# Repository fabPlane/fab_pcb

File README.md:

Images referenced from the description of fabPlane/fab_pcb PR #34 (kept off main).

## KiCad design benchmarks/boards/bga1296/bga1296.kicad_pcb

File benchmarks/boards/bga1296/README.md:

# Eight-layer 1,296-net BGA keepout candidate

Original MIT fixture, seed 6596. A 36 × 36 BGA at 0.5 mm pitch drives
1,296 shuffled two-terminal nets to four destination banks (2,592 pads total).
The 90 × 90 mm board has eight signal copper layers, 0.10/0.10 mm track/clearance
and 0.30/0.10 mm through vias. Two 3 × 28 mm routing keepouts at x=29–32 and
x=58–61, y=31–59 forbid tracks and vias on every copper layer. Routes can pass
around their ends. This increases input size and adds constraints relative to
the earlier 1,024-net candidate; relative routing difficulty is not established.

The companion project is required. No planes, differential pairs, matched
lengths, footprint libraries or external board sources are used. The generator
loads the board, checks net ownership, stack, effective rules, rule-area masks,
and native connectivity, then runs a fresh native DRC. It also requires all 16
keepout polygons in the exported DSN, with exact micrometre coordinates,
layer multiplicity, zero aperture, and closed rectangular vertex sequences.
This fixture-specific check intentionally rejects alternate export grammars. Board, project and DSN are deterministic
across output directories.

KiCad 10.0.6 reports 1,296 native connectivity opens but caps the DRC JSON at
499 unconnected findings. The zero geometry errors and warnings admit the input;
the capped report does not establish exact routed opens or native completion.
There is no best-known complete, DRC-clean routing yet. Keep this board outside
the frozen suite and do not promote it to a feasible scored tier.

## Generate and verify

Requires `/usr/bin/python3` with `pcbnew`, and `kicad-cli` 10.0.6. Use a fresh output
directory. No network access is needed.

```sh
nice -n 10 taskset -c 0-5 timeout 150 /usr/bin/python3 -O benchmarks/boards/bga1296/generate.py /tmp/bga1296-new --seed 6596
nice -n 10 taskset -c 0-5 timeout 180 /usr/bin/python3 -O -m unittest discover -s benchmarks/boards/bga1296 -p 'test_*.py'
```

The measurement compares the same placement, nets, seed and rules with and
without the two keepouts, three fresh runs per router and variant. Full-corpus
measurements preserve the existing five bundled suites. See the PR assets for
exact source pins, results and limitations. Native baseline denominator adoption
remains pending; this fixture does not change scoring or ranking.

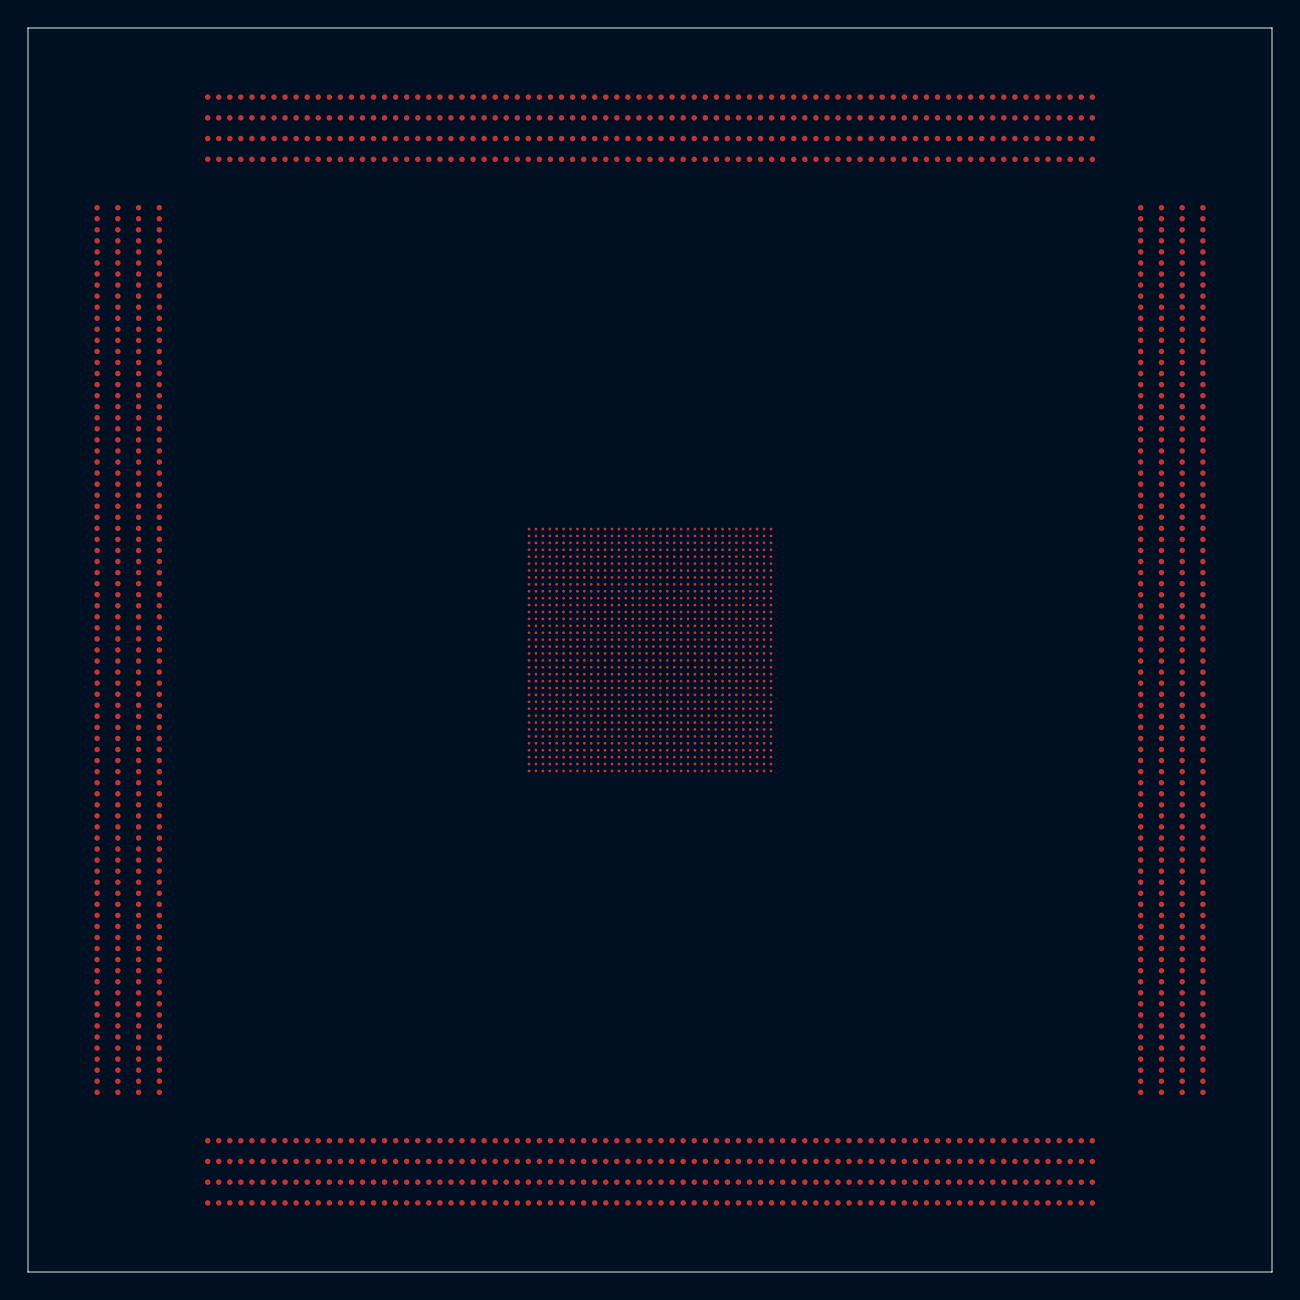
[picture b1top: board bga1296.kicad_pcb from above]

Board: 8 copper layers, 90.0 x 90.0 mm, 1297 parts (0 on the bottom side), 1296 nets, no tracks yet.

Parts:
J1, J2, J3, J4, J5, J6, J7, J8, J9, J10, J11, J12, J13, J14, J15, J16, J17, J18, J19, J20, J21, J22, J23, J24, J25, J26, J27, J28, J29, J30, J31, J32, J33, J34, J35, J36, J37, J38, J39, J40, J41, J42, J43, J44, J45, J46, J47, J48, J49, J50, J51, J52, J53, J54, J55, J56, J57, J58, J59, J60, J61, J62, J63, J64, J65, J66, J67, J68, J69, J70, J71, J72, J73, J74, J75, J76, J77, J78, J79, J80, J81, J82, J83, J84, J85, J86, J87, J88, J89, J90, J91, J92, J93, J94, J95, J96, J97, J98, J99, J100, J101, J102, J103, J104, J105, J106, J107, J108, J109, J110, J111, J112, J113, J114, J115, J116, J117, J118, J119, J120, J121, J122, J123, J124, J125, J126, J127, J128, J129, J130, J131, J132, J133, J134, J135, J136, J137, J138, J139, J140, J141, J142, J143, J144, J145, J146, J147, J148, J149, J150, J151, J152, J153, J154, J155, J156, J157, J158, J159, J160, J161, J162, J163, J164, J165, J166, J167, J168, J169, J170, J171, J172, J173, J174, J175, J176, J177, J178, J179, J180, J181, J182, J183, J184, J185, J186, J187, J188, J189, J190, J191, J192, J193, J194, J195, J196, J197, J198, J199, J200, J201, J202, J203, J204, J205, J206, J207, J208, J209, J210, J211, J212, J213, J214, J215, J216, J217, J218, J219, J220, J221, J222, J223, J224, J225, J226, J227, J228, J229, J230, J231, J232, J233, J234, J235, J236, J237, J238, J239, J240, J241, J242, J243, J244, J245, J246, J247, J248, J249, J250, J251, J252, J253, J254, J255, J256, J257, J258, J259, J260, J261, J262, J263, J264, J265, J266, J267, J268, J269, J270, J271, J272, J273, J274, J275, J276, J277, J278, J279, J280, J281, J282, J283, J284, J285, J286, J287, J288, J289, J290, J291, J292, J293, J294, J295, J296, J297, J298, J299, J300, J301, J302, J303, J304, J305, J306, J307, J308, J309, J310, J311, J312, J313, J314, J315, J316, J317, J318, J319, J320, J321, J322, J323, J324, J325, J326, J327, J328, J329, J330, J331, J332, J333, J334, J335, J336, J337, J338, J339, J340, J341, J342, J343, J344, J345, J346, J347, J348, J349, J350, J351, J352, J353, J354, J355, J356, J357, J358, J359, J360, J361, J362, J363, J364, J365, J366, J367, J368, J369, J370, J371, J372, J373, J374, J375, J376, J377, J378, J379, J380, J381, J382, J383, J384, J385, J386, J387, J388, J389, J390, J391, J392, J393, J394, J395, J396, J397, J398, J399, J400, J401, J402, J403, J404, J405, J406, J407, J408, J409, J410, J411, J412, J413, J414, J415, J416, J417, J418, J419, J420, J421, J422, J423, J424, J425, J426, J427, J428, J429, J430, J431, J432, J433, J434, J435, J436, J437, J438, J439, J440, J441, J442, J443, J444, J445, J446, J447, J448, J449, J450, J451, J452, J453, J454, J455, J456, J457, J458, J459, J460, J461, J462, J463, J464, J465, J466, J467, J468, J469, J470, J471, J472, J473, J474, J475, J476, J477, J478, J479, J480, J481, J482, J483, J484, J485, J486, J487, J488, J489, J490, J491, J492, J493, J494, J495, J496, J497, J498, J499, J500, J501, J502, J503, J504, J505, J506, J507, J508, J509, J510, J511, J512, J513, J514, J515, J516, J517, J518, J519, J520, J521, J522, J523, J524, J525, J526, J527, J528, J529, J530, J531, J532, J533, J534, J535, J536, J537, J538, J539, J540, J541, J542, J543, J544, J545, J546, J547, J548, J549, J550, J551, J552, J553, J554, J555, J556, J557, J558, J559, J560, J561, J562, J563, J564, J565, J566, J567, J568, J569, J570, J571, J572, J573, J574, J575, J576, J577, J578, J579, J580, J581, J582, J583, J584, J585, J586, J587, J588, J589, J590, J591, J592, J593, J594, J595, J596, J597, J598, J599, J600, J601, J602, J603, J604, J605, J606, J607, J608, J609, J610, J611, J612, J613, J614, J615, J616, J617, J618, J619, J620, J621, J622, J623, J624, J625, J626, J627, J628, J629, J630, J631, J632, J633, J634, J635, J636, J637, J638, J639, J640, J641, J642, J643, J644, J645, J646, J647, J648, J649, J650, J651, J652, J653, J654, J655, J656, J657, J658, J659, J660, J661, J662, J663, J664, J665, J666, J667, J668, J669, J670, J671, J672, J673, J674, J675, J676, J677, J678, J679, J680, J681, J682, J683, J684, J685, J686, J687, J688, J689, J690, J691, J692, J693, J694, J695, J696, J697, J698, J699, J700, J701, J702, J703, J704, J705, J706, J707, J708, J709, J710, J711, J712, J713, J714, J715, J716, J717, J718, J719, J720, J721, J722, J723, J724, J725, J726, J727, J728, J729, J730, J731, J732, J733, J734, J735, J736, J737, J738, J739, J740, J741, J742, J743, J744, J745, J746, J747, J748, J749, J750, J751, J752, J753, J754, J755, J756, J757, J758, J759, J760, J761, J762, J763, J764, J765, J766, J767, J768, J769, J770, J771, J772, J773, J774, J775, J776, J777, J778, J779, J780, J781, J782, J783, J784, J785, J786, J787, J788, J789, J790, J791, J792, J793, J794, J795, J796, J797, J798, J799, J800, J801, J802, J803, J804, J805, J806, J807, J808, J809, J810, J811, J812, J813, J814, J815, J816, J817, J818, J819, J820, J821, J822, J823, J824, J825, J826, J827, J828, J829, J830, J831, J832, J833, J834, J835, J836, J837, J838, J839, J840, J841, J842, J843, J844, J845, J846, J847, J848, J849, J850, J851, J852, J853, J854, J855, J856, J857, J858, J859, J860, J861, J862, J863, J864, J865, J866, J867, J868, J869, J870, J871, J872, J873, J874, J875, J876, J877, J878, J879, J880, J881, J882, J883, J884, J885, J886, J887, J888, J889, J890, J891, J892, J893, J894, J895, J896, J897, J898, J899, J900, J901, J902, J903, J904, J905, J906, J907, J908, J909, J910, J911, J912, J913, J914, J915, J916, J917, J918, J919, J920, J921, J922, J923, J924, J925, J926, J927, J928, J929, J930, J931, J932, J933, J934, J935, J936, J937, J938, J939, J940, J941, J942, J943, J944, J945, J946, J947, J948, J949, J950, J951, J952, J953, J954, J955, J956, J957, J958, J959, J960, J961, J962, J963, J964, J965, J966, J967, J968, J969, J970, J971, J972, J973, J974, J975, J976, J977, J978, J979, J980, J981, J982, J983, J984, J985, J986, J987, J988, J989, J990, J991, J992, J993, J994, J995, J996, J997, J998, J999, J1000, J1001, J1002, J1003, J1004, J1005, J1006, J1007, J1008, J1009, J1010, J1011, J1012, J1013, J1014, J1015, J1016, J1017, J1018, J1019, J1020, J1021, J1022, J1023, J1024, J1025, J1026, J1027, J1028, J1029, J1030, J1031, J1032, J1033, J1034, J1035, J1036, J1037, J1038, J1039, J1040, J1041, J1042, J1043, J1044, J1045, J1046, J1047, J1048, J1049, J1050, J1051, J1052, J1053, J1054, J1055, J1056, J1057, J1058, J1059, J1060, J1061, J1062, J1063, J1064, J1065, J1066, J1067, J1068, J1069, J1070, J1071, J1072, J1073, J1074, J1075, J1076, J1077, J1078, J1079, J1080, J1081, J1082, J1083, J1084, J1085, J1086, J1087, J1088, J1089, J1090, J1091, J1092, J1093, J1094, J1095, J1096, J1097, J1098, J1099, J1100, J1101, J1102, J1103, J1104, J1105, J1106, J1107, J1108, J1109, J1110, J1111, J1112, J1113, J1114, J1115, J1116, J1117, J1118, J1119, J1120, J1121, J1122, J1123, J1124, J1125, J1126, J1127, J1128, J1129, J1130, J1131, J1132, J1133, J1134, J1135, J1136, J1137, J1138, J1139, J1140, J1141, J1142, J1143, J1144, J1145, J1146, J1147, J1148, J1149, J1150, J1151, J1152, J1153, J1154, J1155, J1156, J1157, J1158, J1159, J1160, J1161, J1162, J1163, J1164, J1165, J1166, J1167, J1168, J1169, J1170, J1171, J1172, J1173, J1174, J1175, J1176, J1177, J1178, J1179, J1180, J1181, J1182, J1183, J1184, J1185, J1186, J1187, J1188, J1189, J1190, J1191, J1192, J1193, J1194, J1195, J1196, J1197, J1198, J1199, J1200, J1201, J1202, J1203, J1204, J1205, J1206, J1207, J1208, J1209, J1210, J1211, J1212, J1213, J1214, J1215, J1216, J1217, J1218, J1219, J1220, J1221, J1222, J1223, J1224, J1225, J1226, J1227, J1228, J1229, J1230, J1231, J1232, J1233, J1234, J1235, J1236, J1237, J1238, J1239, J1240, J1241, J1242, J1243, J1244, J1245, J1246, J1247, J1248, J1249, J1250, J1251, J1252, J1253, J1254, J1255, J1256, J1257, J1258, J1259, J1260, J1261, J1262, J1263, J1264, J1265, J1266, J1267, J1268, J1269, J1270, J1271, J1272, J1273, J1274, J1275, J1276, J1277, J1278, J1279, J1280, J1281, J1282, J1283, J1284, J1285, J1286, J1287, J1288, J1289, J1290, J1291, J1292, J1293, J1294, J1295, J1296: escape
U1: escape

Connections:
N1: J1202.1, U1.1
N2: J1135.2, U1.2
N3: J41.3, U1.3
N4: J443.4, U1.4
N5: J1162.5, U1.5
N6: J767.6, U1.6
N7: J1284.7, U1.7
N8: J728.8, U1.8
N9: J1100.9, U1.9
N10: J513.10, U1.10
N11: J958.11, U1.11
N12: J603.12, U1.12
N13: J329.13, U1.13
N14: J803.14, U1.14
N15: J801.15, U1.15
N16: J155.16, U1.16
N17: J181.17, U1.17
N18: J424.18, U1.18
N19: J180.19, U1.19
N20: J281.20, U1.20
N21: J758.21, U1.21
N22: J1275.22, U1.22
N23: J203.23, U1.23
N24: J595.24, U1.24
N25: J113.25, U1.25
N26: J304.26, U1.26
N27: J1211.27, U1.27
N28: J1267.28, U1.28
N29: J76.29, U1.29
N30: J81.30, U1.30
N31: J237.31, U1.31
N32: J370.32, U1.32
N33: J895.33, U1.33
N34: J582.34, U1.34
N35: J457.35, U1.35
N36: J177.36, U1.36
N37: J532.37, U1.37
N38: J393.38, U1.38
N39: J289.39, U1.39
N40: J999.40, U1.40
N41: J422.41, U1.41
N42: J683.42, U1.42
N43: J322.43, U1.43
N44: J1190.44, U1.44
N45: J134.45, U1.45
N46: J189.46, U1.46
N47: J230.47, U1.47
N48: J609.48, U1.48
N49: J735.49, U1.49
N50: J769.50, U1.50
N51: J1065.51, U1.51
N52: J52.52, U1.52
N53: J696.53, U1.53
N54: J480.54, U1.54
N55: J107.55, U1.55
N56: J784.56, U1.56
N57: J431.57, U1.57
N58: J1257.58, U1.58
N59: J160.59, U1.59
N60: J520.60, U1.60
N61: J5.61, U1.61
N62: J1006.62, U1.62
N63: J347.63, U1.63
N64: J666.64, U1.64
N65: J255.65, U1.65
N66: J737.66, U1.66
N67: J19.67, U1.67
N68: J56.68, U1.68
N69: J601.69, U1.69
N70: J732.70, U1.70
N71: J676.71, U1.71
N72: J471.72, U1.72
N73: J1132.73, U1.73
N74: J643.74, U1.74
N75: J944.75, U1.75
N76: J268.76, U1.76
N77: J283.77, U1.77
N78: J556.78, U1.78
N79: J939.79, U1.79
N80: J1161.80, U1.80
N81: J587.81, U1.81
N82: J573.82, U1.82
N83: J1252.83, U1.83
N84: J641.84, U1.84
N85: J1.85, U1.85
N86: J1180.86, U1.86
N87: J709.87, U1.87
N88: J806.88, U1.88
N89: J1091.89, U1.89
N90: J647.90, U1.90
N91: J636.91, U1.91
N92: J519.92, U1.92
N93: J239.93, U1.93
N94: J1246.94, U1.94
N95: J1136.95, U1.95
N96: J292.96, U1.96
N97: J907.97, U1.97
N98: J14.98, U1.98
N99: J120.99, U1.99
N100: J990.100, U1.100
N101: J71.101, U1.101
N102: J179.102, U1.102
N103: J812.103, U1.103
N104: J1208.104, U1.104
N105: J1134.105, U1.105
N106: J555.106, U1.106
N107: J738.107, U1.107
N108: J651.108, U1.108
N109: J320.109, U1.109
N110: J223.110, U1.110
N111: J1201.111, U1.111
N112: J716.112, U1.112
N113: J466.113, U1.113
N114: J876.114, U1.114
N115: J844.115, U1.115
N116: J330.116, U1.116
N117: J881.117, U1.117
N118: J1080.118, U1.118
N119: J1056.119, U1.119
N120: J454.120, U1.120
N121: J761.121, U1.121
N122: J64.122, U1.122
N123: J94.123, U1.123
N124: J352.124, U1.124
N125: J339.125, U1.125
N126: J848.126, U1.126
N127: J750.127, U1.127
N128: J580.128, U1.128
N129: J973.129, U1.129
N130: J47.130, U1.130
N131: J224.131, U1.131
N132: J384.132, U1.132
N133: J778.133, U1.133
N134: J91.134, U1.134
N135: J730.135, U1.135
N136: J215.136, U1.136
N137: J987.137, U1.137
N138: J649.138, U1.138
N139: J1207.139, U1.139
N140: J798.140, U1.140
N141: J793.141, U1.141
N142: J510.142, U1.142
N143: J410.143, U1.143
N144: J518.144, U1.144
N145: J1148.145, U1.145
N146: J524.146, U1.146
N147: J398.147, U1.147
N148: J48.148, U1.148
N149: J1103.149, U1.149
N150: J198.150, U1.150
N151: J219.151, U1.151
N152: J1023.152, U1.152
N153: J397.153, U1.153
N154: J984.154, U1.154
N155: J479.155, U1.155
N156: J620.156, U1.156
N157: J1034.157, U1.157
N158: J204.158, U1.158
N159: J218.159, U1.159
N160: J305.160, U1.160
N161: J606.161, U1.161
N162: J993.162, U1.162
N163: J364.163, U1.163
N164: J618.164, U1.164
N165: J625.165, U1.165
N166: J824.166, U1.166
N167: J724.167, U1.167
N168: J1019.168, U1.168
N169: J1247.169, U1.169
N170: J75.170, U1.170
N171: J462.171, U1.171
N172: J202.172, U1.172
N173: J245.173, U1.173
N174: J1159.174, U1.174
N175: J949.175, U1.175
N176: J612.176, U1.176
N177: J660.177, U1.177
N178: J61.178, U1.178
N179: J909.179, U1.179
N180: J1266.180, U1.180
N181: J428.181, U1.181
N182: J331.182, U1.182
N183: J127.183, U1.183
N184: J919.184, U1.184
N185: J506.185, U1.185
N186: J220.186, U1.186
N187: J726.187, U1.187
N188: J866.188, U1.188
N189: J1005.189, U1.189
N190: J579.190, U1.190
N191: J1116.191, U1.191
N192: J187.192, U1.192
N193: J539.193, U1.193
N194: J487.194, U1.194
N195: J3.195, U1.195
N196: J1092.196, U1.196
N197: J264.197, U1.197
N198: J903.198, U1.198
N199: J557.199, U1.199
N200: J871.200, U1.200
N201: J926.201, U1.201
N202: J183.202, U1.202
N203: J1182.203, U1.203
N204: J599.204, U1.204
N205: J1272.205, U1.205
N206: J829.206, U1.206
N207: J1288.207, U1.207
N208: J282.208, U1.208
N209: J805.209, U1.209
N210: J135.210, U1.210
N211: J1184.211, U1.211
N212: J995.212, U1.212
N213: J197.213, U1.213
N214: J1166.214, U1.214
N215: J401.215, U1.215
N216: J314.216, U1.216
N217: J163.217, U1.217
N218: J207.218, U1.218
N219: J1229.219, U1.219
N220: J797.220, U1.220
N221: J743.221, U1.221
N222: J54.222, U1.222
N223: J781.223, U1.223
N224: J413.224, U1.224
N225: J791.225, U1.225
N226: J1081.226, U1.226
N227: J646.227, U1.227
N228: J937.228, U1.228
N229: J808.229, U1.229
N230: J945.230, U1.230
N231: J543.231, U1.231
N232: J445.232, U1.232
N233: J795.233, U1.233
N234: J671.234, U1.234
N235: J988.235, U1.235
N236: J1048.236, U1.236
N237: J1181.237, U1.237
N238: J131.238, U1.238
N239: J605.239, U1.239
N240: J835.240, U1.240
N241: J392.241, U1.241
N242: J1082.242, U1.242
N243: J1094.243, U1.243
N244: J544.244, U1.244
N245: J167.245, U1.245
N246: J1283.246, U1.246
N247: J1012.247, U1.247
N248: J780.248, U1.248
N249: J1164.249, U1.249
N250: J1088.250, U1.250
N251: J232.251, U1.251
N252: J132.252, U1.252
N253: J699.253, U1.253
N254: J614.254, U1.254
N255: J669.255, U1.255
N256: J418.256, U1.256
N257: J877.257, U1.257
N258: J228.258, U1.258
N259: J1111.259, U1.259
N260: J626.260, U1.260
N261: J924.261, U1.261
N262: J151.262, U1.262
N263: J51.263, U1.263
N264: J191.264, U1.264
N265: J115.265, U1.265
N266: J463.266, U1.266
N267: J108.267, U1.267
N268: J832.268, U1.268
N269: J291.269, U1.269
N270: J863.270, U1.270
N271: J1292.271, U1.271
N272: J634.272, U1.272
N273: J157.273, U1.273
N274: J749.274, U1.274
N275: J1240.275, U1.275
N276: J790.276, U1.276
N277: J1152.277, U1.277
N278: J981.278, U1.278
N279: J564.279, U1.279
N280: J34.280, U1.280
N281: J1075.281, U1.281
N282: J1253.282, U1.282
N283: J745.283, U1.283
N284: J176.284, U1.284
N285: J980.285, U1.285
N286: J920.286, U1.286
N287: J495.287, U1.287
N288: J22.288, U1.288
N289: J529.289, U1.289
N290: J60.290, U1.290
N291: J1168.291, U1.291
N292: J150.292, U1.292
N293: J540.293, U1.293
N294: J830.294, U1.294
N295: J1055.295, U1.295
N296: J284.296, U1.296
N297: J545.297, U1.297
N298: J366.298, U1.298
N299: J584.299, U1.299
N300: J604.300, U1.300
N301: J1123.301, U1.301
N302: J295.302, U1.302
N303: J1013.303, U1.303
N304: J10.304, U1.304
N305: J1196.305, U1.305
N306: J355.306, U1.306
N307: J43.307, U1.307
N308: J405.308, U1.308
N309: J1020.309, U1.309
N310: J712.310, U1.310
N311: J188.311, U1.311
N312: J23.312, U1.312
N313: J533.313, U1.313
N314: J412.314, U1.314
N315: J814.315, U1.315
N316: J396.316, U1.316
N317: J468.317, U1.317
N318: J616.318, U1.318
N319: J1261.319, U1.319
N320: J1194.320, U1.320
N321: J1172.321, U1.321
N322: J222.322, U1.322
N323: J380.323, U1.323
N324: J912.324, U1.324
N325: J1280.325, U1.325
N326: J125.326, U1.326
N327: J1047.327, U1.327
N328: J55.328, U1.328
N329: J998.329, U1.329
N330: J1015.330, U1.330
N331: J325.331, U1.331
N332: J139.332, U1.332
N333: J129.333, U1.333
N334: J748.334, U1.334
N335: J757.335, U1.335
N336: J201.336, U1.336
N337: J702.337, U1.337
N338: J893.338, U1.338
N339: J1030.339, U1.339
N340: J629.340, U1.340
N341: J968.341, U1.341
N342: J1289.342, U1.342
N343: J515.343, U1.343
N344: J1133.344, U1.344
N345: J1241.345, U1.345
N346: J1222.346, U1.346
N347: J619.347, U1.347
N348: J589.348, U1.348
N349: J742.349, U1.349
N350: J534.350, U1.350
N351: J652.351, U1.351
N352: J501.352, U1.352
N353: J837.353, U1.353
N354: J1035.354, U1.354
N355: J1044.355, U1.355
N356: J451.356, U1.356
N357: J1064.357, U1.357
N358: J890.358, U1.358
N359: J560.359, U1.359
N360: J1173.360, U1.360
N361: J478.361, U1.361
N362: J20.362, U1.362
N363: J271.363, U1.363
N364: J434.364, U1.364
N365: J1058.365, U1.365
N366: J263.366, U1.366
N367: J474.367, U1.367
N368: J96.368, U1.368
N369: J33.369, U1.369
N370: J936.370, U1.370
N371: J278.371, U1.371
N372: J685.372, U1.372
N373: J152.373, U1.373
N374: J159.374, U1.374
N375: J729.375, U1.375
N376: J1217.376, U1.376
N377: J1188.377, U1.377
N378: J1286.378, U1.378
N379: J960.379, U1.379
N380: J123.380, U1.380
N381: J421.381, U1.381
N382: J657.382, U1.382
N383: J1039.383, U1.383
N384: J838.384, U1.384
N385: J381.385, U1.385
N386: J1221.386, U1.386
N387: J734.387, U1.387
N388: J161.388, U1.388
N389: J280.389, U1.389
N390: J959.390, U1.390
N391: J1230.391, U1.391
N392: J933.392, U1.392
N393: J99.393, U1.393
N394: J1226.394, U1.394
N395: J1138.395, U1.395
N396: J7.396, U1.396
N397: J916.397, U1.397
N398: J1179.398, U1.398
N399: J404.399, U1.399
N400: J575.400, U1.400
N401: J588.401, U1.401
N402: J483.402, U1.402
N403: J1090.403, U1.403
N404: J78.404, U1.404
N405: J137.405, U1.405
N406: J70.406, U1.406
N407: J200.407, U1.407
N408: J678.408, U1.408
N409: J240.409, U1.409
N410: J1071.410, U1.410
N411: J242.411, U1.411
N412: J121.412, U1.412
N413: J1139.413, U1.413
N414: J846.414, U1.414
N415: J118.415, U1.415
N416: J194.416, U1.416
N417: J762.417, U1.417
N418: J836.418, U1.418
N419: J1228.419, U1.419
N420: J896.420, U1.420
N421: J270.421, U1.421
N422: J1198.422, U1.422
N423: J1066.423, U1.423
N424: J760.424, U1.424
N425: J452.425, U1.425
N426: J528.426, U1.426
N427: J338.427, U1.427
N428: J684.428, U1.428
N429: J235.429, U1.429
N430: J217.430, U1.430
N431: J755.431, U1.431
N432: J427.432, U1.432
N433: J917.433, U1.433
N434: J753.434, U1.434
N435: J782.435, U1.435
N436: J1171.436, U1.436
N437: J842.437, U1.437
N438: J1126.438, U1.438
N439: J694.439, U1.439
N440: J8.440, U1.440
N441: J752.441, U1.441
N442: J376.442, U1.442
N443: J433.443, U1.443
N444: J929.444, U1.444
N445: J17.445, U1.445
N446: J286.446, U1.446
N447: J928.447, U1.447
N448: J1129.448, U1.448
N449: J862.449, U1.449
N450: J617.450, U1.450
N451: J1069.451, U1.451
N452: J1141.452, U1.452
N453: J856.453, U1.453
N454: J809.454, U1.454
N455: J158.455, U1.455
N456: J548.456, U1.456
N457: J1167.457, U1.457
N458: J1220.458, U1.458
N459: J1016.459, U1.459
N460: J368.460, U1.460
N461: J963.461, U1.461
N462: J460.462, U1.462
N463: J883.463, U1.463
N464: J1263.464, U1.464
N465: J1086.465, U1.465
N466: J374.466, U1.466
N467: J21.467, U1.467
N468: J1189.468, U1.468
N469: J1193.469, U1.469
N470: J568.470, U1.470
N471: J97.471, U1.471
N472: J414.472, U1.472
N473: J103.473, U1.473
N474: J1131.474, U1.474
N475: J562.475, U1.475
N476: J133.476, U1.476
N477: J517.477, U1.477
N478: J786.478, U1.478
N479: J1045.479, U1.479
N480: J792.480, U1.480
N481: J136.481, U1.481
N482: J485.482, U1.482
N483: J1149.483, U1.483
N484: J1002.484, U1.484
N485: J229.485, U1.485
N486: J455.486, U1.486
N487: J635.487, U1.487
N488: J402.488, U1.488
N489: J908.489, U1.489
N490: J67.490, U1.490
N491: J15.491, U1.491
N492: J372.492, U1.492
N493: J1254.493, U1.493
N494: J1106.494, U1.494
N495: J265.495, U1.495
N496: J718.496, U1.496
N497: J1279.497, U1.497
N498: J186.498, U1.498
N499: J32.499, U1.499
N500: J756.500, U1.500
N501: J947.501, U1.501
N502: J36.502, U1.502
N503: J913.503, U1.503
N504: J914.504, U1.504
N505: J326.505, U1.505
N506: J875.506, U1.506
N507: J59.507, U1.507
N508: J994.508, U1.508
N509: J464.509, U1.509
N510: J833.510, U1.510
N511: J845.511, U1.511
N512: J613.512, U1.512
N513: J1199.513, U1.513
N514: J50.514, U1.514
N515: J682.515, U1.515
N516: J759.516, U1.516
N517: J549.517, U1.517
N518: J439.518, U1.518
N519: J811.519, U1.519
N520: J563.520, U1.520
N521: J1183.521, U1.521
N522: J1040.522, U1.522
N523: J111.523, U1.523
N524: J898.524, U1.524
N525: J141.525, U1.525
N526: J53.526, U1.526
N527: J226.527, U1.527
N528: J764.528, U1.528
N529: J731.529, U1.529
N530: J567.530, U1.530
N531: J628.531, U1.531
N532: J456.532, U1.532
N533: J538.533, U1.533
N534: J1004.534, U1.534
N535: J508.535, U1.535
N536: J521.536, U1.536
N537: J1276.537, U1.537
N538: J306.538, U1.538
N539: J1121.539, U1.539
N540: J516.540, U1.540
N541: J607.541, U1.541
N542: J92.542, U1.542
N543: J1028.543, U1.543
N544: J872.544, U1.544
N545: J680.545, U1.545
N546: J541.546, U1.546
N547: J583.547, U1.547
N548: J704.548, U1.548
N549: J1140.549, U1.549
N550: J873.550, U1.550
N551: J1052.551, U1.551
N552: J623.552, U1.552
N553: J700.553, U1.553
N554: J714.554, U1.554
N555: J815.555, U1.555
N556: J550.556, U1.556
N557: J536.557, U1.557
N558: J2.558, U1.558
N559: J739.559, U1.559
N560: J774.560, U1.560
N561: J1197.561, U1.561
N562: J779.562, U1.562
N563: J922.563, U1.563
N564: J820.564, U1.564
N565: J250.565, U1.565
N566: J31.566, U1.566
N567: J927.567, U1.567
N568: J328.568, U1.568
N569: J715.569, U1.569
N570: J717.570, U1.570
N571: J319.571, U1.571
N572: J300.572, U1.572
N573: J1233.573, U1.573
N574: J834.574, U1.574
N575: J509.575, U1.575
N576: J11.576, U1.576
N577: J858.577, U1.577
N578: J367.578, U1.578
N579: J955.579, U1.579
N580: J840.580, U1.580
N581: J956.581, U1.581
N582: J1054.582, U1.582
N583: J440.583, U1.583
N584: J481.584, U1.584
N585: J950.585, U1.585
N586: J437.586, U1.586
N587: J430.587, U1.587
N588: J861.588, U1.588
N589: J853.589, U1.589
N590: J458.590, U1.590
N591: J1234.591, U1.591
N592: J73.592, U1.592
N593: J1259.593, U1.593
N594: J1127.594, U1.594
N595: J1242.595, U1.595
N596: J285.596, U1.596
N597: J1243.597, U1.597
N598: J390.598, U1.598
N599: J878.599, U1.599
N600: J105.600, U1.600
N601: J425.601, U1.601
N602: J891.602, U1.602
N603: J1032.603, U1.603
N604: J662.604, U1.604
N605: J493.605, U1.605
N606: J407.606, U1.606
N607: J1085.607, U1.607
N608: J935.608, U1.608
N609: J426.609, U1.609
N610: J692.610, U1.610
N611: J578.611, U1.611
N612: J1036.612, U1.612
N613: J294.613, U1.613
N614: J205.614, U1.614
N615: J721.615, U1.615
N616: J659.616, U1.616
N617: J503.617, U1.617
N618: J542.618, U1.618
N619: J1074.619, U1.619
N620: J1271.620, U1.620
N621: J1249.621, U1.621
N622: J100.622, U1.622
N623: J530.623, U1.623
N624: J85.624, U1.624
N625: J482.625, U1.625
N626: J335.626, U1.626
N627: J706.627, U1.627
N628: J46.628, U1.628
N629: J37.629, U1.629
N630: J312.630, U1.630
N631: J523.631, U1.631
N632: J432.632, U1.632
N633: J624.633, U1.633
N634: J236.634, U1.634
N635: J695.635, U1.635
N636: J336.636, U1.636
N637: J910.637, U1.637
N638: J450.638, U1.638
N639: J469.639, U1.639
N640: J299.640, U1.640
N641: J585.641, U1.641
N642: J477.642, U1.642
N643: J138.643, U1.643
N644: J865.644, U1.644
N645: J979.645, U1.645
N646: J446.646, U1.646
N647: J1038.647, U1.647
N648: J470.648, U1.648
N649: J216.649, U1.649
N650: J342.650, U1.650
N651: J4.651, U1.651
N652: J1287.652, U1.652
N653: J1128.653, U1.653
N654: J112.654, U1.654
N655: J1042.655, U1.655
N656: J221.656, U1.656
N657: J313.657, U1.657
N658: J886.658, U1.658
N659: J1290.659, U1.659
N660: J642.660, U1.660
N661: J214.661, U1.661
N662: J486.662, U1.662
N663: J210.663, U1.663
N664: J79.664, U1.664
N665: J1260.665, U1.665
N666: J594.666, U1.666
N667: J1177.667, U1.667
N668: J472.668, U1.668
N669: J1296.669, U1.669
N670: J44.670, U1.670
N671: J148.671, U1.671
N672: J667.672, U1.672
N673: J438.673, U1.673
N674: J95.674, U1.674
N675: J170.675, U1.675
N676: J1203.676, U1.676
N677: J259.677, U1.677
N678: J650.678, U1.678
N679: J1061.679, U1.679
N680: J1077.680, U1.680
N681: J1251.681, U1.681
N682: J16.682, U1.682
N683: J119.683, U1.683
N684: J296.684, U1.684
N685: J1239.685, U1.685
N686: J346.686, U1.686
N687: J703.687, U1.687
N688: J1093.688, U1.688
N689: J771.689, U1.689
N690: J1049.690, U1.690
N691: J989.691, U1.691
N692: J1083.692, U1.692
N693: J327.693, U1.693
N694: J484.694, U1.694
N695: J547.695, U1.695
N696: J88.696, U1.696
N697: J600.697, U1.697
N698: J813.698, U1.698
N699: J992.699, U1.699
N700: J87.700, U1.700
N701: J149.701, U1.701
N702: J246.702, U1.702
N703: J768.703, U1.703
N704: J1130.704, U1.704
N705: J379.705, U1.705
N706: J1007.706, U1.706
N707: J638.707, U1.707
N708: J864.708, U1.708
N709: J1084.709, U1.709
N710: J648.710, U1.710
N711: J344.711, U1.711
N712: J796.712, U1.712
N713: J321.713, U1.713
N714: J1268.714, U1.714
N715: J1154.715, U1.715
N716: J964.716, U1.716
N717: J1245.717, U1.717
N718: J310.718, U1.718
N719: J1144.719, U1.719
N720: J140.720, U1.720
N721: J1010.721, U1.721
N722: J969.722, U1.722
N723: J193.723, U1.723
N724: J997.724, U1.724
N725: J195.725, U1.725
N726: J494.726, U1.726
N727: J211.727, U1.727
N728: J358.728, U1.728
N729: J611.729, U1.729
N730: J359.730, U1.730
N731: J1258.731, U1.731
N732: J653.732, U1.732
N733: J274.733, U1.733
N734: J316.734, U1.734
N735: J1060.735, U1.735
N736: J110.736, U1.736
N737: J406.737, U1.737
N738: J852.738, U1.738
N739: J565.739, U1.739
N740: J670.740, U1.740
N741: J507.741, U1.741
N742: J349.742, U1.742
N743: J823.743, U1.743
N744: J1050.744, U1.744
N745: J303.745, U1.745
N746: J942.746, U1.746
N747: J597.747, U1.747
N748: J932.748, U1.748
N749: J831.749, U1.749
N750: J552.750, U1.750
N751: J38.751, U1.751
N752: J1063.752, U1.752
N753: J1008.753, U1.753
N754: J931.754, U1.754
N755: J114.755, U1.755
N756: J1117.756, U1.756
N757: J802.757, U1.757
N758: J24.758, U1.758
N759: J1115.759, U1.759
N760: J816.760, U1.760
N761: J859.761, U1.761
N762: J627.762, U1.762
N763: J1163.763, U1.763
N764: J411.764, U1.764
N765: J860.765, U1.765
N766: J668.766, U1.766
N767: J633.767, U1.767
N768: J166.768, U1.768
N769: J826.769, U1.769
N770: J953.770, U1.770
N771: J899.771, U1.771
N772: J1178.772, U1.772
N773: J459.773, U1.773
N774: J147.774, U1.774
N775: J733.775, U1.775
N776: J586.776, U1.776
N777: J943.777, U1.777
N778: J62.778, U1.778
N779: J182.779, U1.779
N780: J904.780, U1.780
N781: J415.781, U1.781
N782: J375.782, U1.782
N783: J991.783, U1.783
N784: J902.784, U1.784
N785: J1282.785, U1.785
N786: J918.786, U1.786
N787: J948.787, U1.787
N788: J1274.788, U1.788
N789: J1270.789, U1.789
N790: J385.790, U1.790
N791: J6.791, U1.791
N792: J122.792, U1.792
N793: J982.793, U1.793
N794: J1213.794, U1.794
N795: J298.795, U1.795
N796: J663.796, U1.796
N797: J874.797, U1.797
N798: J124.798, U1.798
N799: J951.799, U1.799
N800: J247.800, U1.800
N801: J156.801, U1.801
N802: J301.802, U1.802
N803: J766.803, U1.803
N804: J722.804, U1.804
N805: J302.805, U1.805
N806: J1053.806, U1.806
N807: J340.807, U1.807
N808: J1285.808, U1.808
N809: J1235.809, U1.809
N810: J257.810, U1.810
N811: J1273.811, U1.811
N812: J885.812, U1.812
N813: J1009.813, U1.813
N814: J467.814, U1.814
N815: J275.815, U1.815
N816: J175.816, U1.816
N817: J162.817, U1.817
N818: J1051.818, U1.818
N819: J723.819, U1.819
N820: J527.820, U1.820
N821: J1224.821, U1.821
N822: J498.822, U1.822
N823: J1195.823, U1.823
N824: J1113.824, U1.824
N825: J499.825, U1.825
N826: J1294.826, U1.826
N827: J25.827, U1.827
N828: J363.828, U1.828
N829: J144.829, U1.829
N830: J128.830, U1.830
N831: J1250.831, U1.831
N832: J505.832, U1.832
N833: J800.833, U1.833
N834: J569.834, U1.834
N835: J1269.835, U1.835
N836: J168.836, U1.836
N837: J658.837, U1.837
N838: J978.838, U1.838
N839: J789.839, U1.839
N840: J1150.840, U1.840
N841: J522.841, U1.841
N842: J546.842, U1.842
N843: J143.843, U1.843
N844: J971.844, U1.844
N845: J511.845, U1.845
N846: J68.846, U1.846
N847: J154.847, U1.847
N848: J884.848, U1.848
N849: J675.849, U1.849
N850: J1205.850, U1.850
N851: J35.851, U1.851
N852: J1114.852, U1.852
N853: J323.853, U1.853
N854: J408.854, U1.854
N855: J287.855, U1.855
N856: J267.856, U1.856
N857: J572.857, U1.857
N858: J827.858, U1.858
N859: J741.859, U1.859
N860: J889.860, U1.860
N861: J1118.861, U1.861
N862: J400.862, U1.862
N863: J630.863, U1.863
N864: J639.864, U1.864
N865: J1265.865, U1.865
N866: J1256.866, U1.866
N867: J49.867, U1.867
N868: J489.868, U1.868
N869: J475.869, U1.869
N870: J435.870, U1.870
N871: J69.871, U1.871
N872: J350.872, U1.872
N873: J248.873, U1.873
N874: J116.874, U1.874
N875: J233.875, U1.875
N876: J681.876, U1.876
N877: J868.877, U1.877
N878: J473.878, U1.878
N879: J351.879, U1.879
N880: J1087.880, U1.880
N881: J857.881, U1.881
N882: J1041.882, U1.882
N883: J318.883, U1.883
N884: J818.884, U1.884
N885: J185.885, U1.885
N886: J80.886, U1.886
N887: J13.887, U1.887
N888: J290.888, U1.888
N889: J419.889, U1.889
N890: J804.890, U1.890
N891: J57.891, U1.891
N892: J386.892, U1.892
N893: J1238.893, U1.893
N894: J1223.894, U1.894
N895: J261.895, U1.895
N896: J985.896, U1.896
N897: J558.897, U1.897
N898: J74.898, U1.898
N899: J258.899, U1.899
N900: J901.900, U1.900
N901: J395.901, U1.901
N902: J610.902, U1.902
N903: J740.903, U1.903
N904: J420.904, U1.904
N905: J785.905, U1.905
N906: J777.906, U1.906
N907: J269.907, U1.907
N908: J1062.908, U1.908
N909: J504.909, U1.909
N910: J1232.910, U1.910
N911: J531.911, U1.911
N912: J708.912, U1.912
N913: J389.913, U1.913
N914: J84.914, U1.914
N915: J525.915, U1.915
N916: J307.916, U1.916
N917: J324.917, U1.917
N918: J561.918, U1.918
N919: J169.919, U1.919
N920: J577.920, U1.920
N921: J98.921, U1.921
N922: J361.922, U1.922
N923: J488.923, U1.923
N924: J277.924, U1.924
N925: J449.925, U1.925
N926: J18.926, U1.926
N927: J514.927, U1.927
N928: J65.928, U1.928
N929: J559.929, U1.929
N930: J787.930, U1.930
N931: J847.931, U1.931
N932: J1209.932, U1.932
N933: J1003.933, U1.933
N934: J843.934, U1.934
N935: J976.935, U1.935
N936: J640.936, U1.936
N937: J526.937, U1.937
N938: J109.938, U1.938
N939: J772.939, U1.939
N940: J1037.940, U1.940
N941: J1137.941, U1.941
N942: J839.942, U1.942
N943: J1043.943, U1.943
N944: J1112.944, U1.944
N945: J701.945, U1.945
N946: J763.946, U1.946
N947: J492.947, U1.947
N948: J677.948, U1.948
N949: J940.949, U1.949
N950: J145.950, U1.950
N951: J394.951, U1.951
N952: J828.952, U1.952
N953: J266.953, U1.953
N954: J776.954, U1.954
N955: J9.955, U1.955
N956: J297.956, U1.956
N957: J719.957, U1.957
N958: J423.958, U1.958
N959: J1147.959, U1.959
N960: J1025.960, U1.960
N961: J106.961, U1.961
N962: J1175.962, U1.962
N963: J497.963, U1.963
N964: J934.964, U1.964
N965: J869.965, U1.965
N966: J357.966, U1.966
N967: J1218.967, U1.967
N968: J174.968, U1.968
N969: J551.969, U1.969
N970: J591.970, U1.970
N971: J854.971, U1.971
N972: J821.972, U1.972
N973: J126.973, U1.973
N974: J674.974, U1.974
N975: J894.975, U1.975
N976: J867.976, U1.976
N977: J962.977, U1.977
N978: J249.978, U1.978
N979: J673.979, U1.979
N980: J276.980, U1.980
N981: J1076.981, U1.981
N982: J966.982, U1.982
N983: J1073.983, U1.983
N984: J906.984, U1.984
N985: J1105.985, U1.985
N986: J104.986, U1.986
N987: J986.987, U1.987
N988: J272.988, U1.988
N989: J1219.989, U1.989
N990: J1107.990, U1.990
N991: J273.991, U1.991
N992: J225.992, U1.992
N993: J977.993, U1.993
N994: J429.994, U1.994
N995: J698.995, U1.995
N996: J930.996, U1.996
N997: J746.997, U1.997
N998: J1185.998, U1.998
N999: J819.999, U1.999
N1000: J192.1000, U1.1000
N1001: J343.1001, U1.1001
N1002: J598.1002, U1.1002
N1003: J142.1003, U1.1003
N1004: J173.1004, U1.1004
N1005: J710.1005, U1.1005
N1006: J1101.1006, U1.1006
N1007: J388.1007, U1.1007
N1008: J554.1008, U1.1008
N1009: J353.1009, U1.1009
N1010: J40.1010, U1.1010
N1011: J365.1011, U1.1011
N1012: J42.1012, U1.1012
N1013: J794.1013, U1.1013
N1014: J1120.1014, U1.1014
N1015: J725.1015, U1.1015
N1016: J1029.1016, U1.1016
N1017: J63.1017, U1.1017
N1018: J655.1018, U1.1018
N1019: J1109.1019, U1.1019
N1020: J1078.1020, U1.1020
N1021: J66.1021, U1.1021
N1022: J101.1022, U1.1022
N1023: J382.1023, U1.1023
N1024: J631.1024, U1.1024
N1025: J436.1025, U1.1025
N1026: J1176.1026, U1.1026
N1027: J850.1027, U1.1027
N1028: J1143.1028, U1.1028
N1029: J672.1029, U1.1029
N1030: J1153.1030, U1.1030
N1031: J965.1031, U1.1031
N1032: J409.1032, U1.1032
N1033: J341.1033, U1.1033
N1034: J1095.1034, U1.1034
N1035: J593.1035, U1.1035
N1036: J1214.1036, U1.1036
N1037: J841.1037, U1.1037
N1038: J880.1038, U1.1038
N1039: J592.1039, U1.1039
N1040: J810.1040, U1.1040
N1041: J256.1041, U1.1041
N1042: J870.1042, U1.1042
N1043: J1070.1043, U1.1043
N1044: J687.1044, U1.1044
N1045: J1236.1045, U1.1045
N1046: J693.1046, U1.1046
N1047: J102.1047, U1.1047
N1048: J1072.1048, U1.1048
N1049: J1059.1049, U1.1049
N1050: J90.1050, U1.1050
N1051: J855.1051, U1.1051
N1052: J254.1052, U1.1052
N1053: J1165.1053, U1.1053
N1054: J28.1054, U1.1054
N1055: J383.1055, U1.1055
N1056: J30.1056, U1.1056
N1057: J209.1057, U1.1057
N1058: J345.1058, U1.1058
N1059: J262.1059, U1.1059
N1060: J1212.1060, U1.1060
N1061: J656.1061, U1.1061
N1062: J851.1062, U1.1062
N1063: J665.1063, U1.1063
N1064: J817.1064, U1.1064
N1065: J334.1065, U1.1065
N1066: J1098.1066, U1.1066
N1067: J975.1067, U1.1067
N1068: J1170.1068, U1.1068
N1069: J720.1069, U1.1069
N1070: J371.1070, U1.1070
N1071: J1022.1071, U1.1071
N1072: J1021.1072, U1.1072
N1073: J1096.1073, U1.1073
N1074: J332.1074, U1.1074
N1075: J691.1075, U1.1075
N1076: J27.1076, U1.1076
N1077: J1102.1077, U1.1077
N1078: J1089.1078, U1.1078
N1079: J1169.1079, U1.1079
N1080: J1024.1080, U1.1080
N1081: J946.1081, U1.1081
N1082: J1186.1082, U1.1082
N1083: J1146.1083, U1.1083
N1084: J690.1084, U1.1084
N1085: J373.1085, U1.1085
N1086: J689.1086, U1.1086
N1087: J1068.1087, U1.1087
N1088: J1000.1088, U1.1088
N1089: J360.1089, U1.1089
N1090: J574.1090, U1.1090
N1091: J231.1091, U1.1091
N1092: J645.1092, U1.1092
N1093: J500.1093, U1.1093
N1094: J615.1094, U1.1094
N1095: J93.1095, U1.1095
N1096: J581.1096, U1.1096
N1097: J879.1097, U1.1097
N1098: J770.1098, U1.1098
N1099: J1033.1099, U1.1099
N1100: J1281.1100, U1.1100
N1101: J354.1101, U1.1101
N1102: J1097.1102, U1.1102
N1103: J1295.1103, U1.1103
N1104: J711.1104, U1.1104
N1105: J1278.1105, U1.1105
N1106: J369.1106, U1.1106
N1107: J208.1107, U1.1107
N1108: J661.1108, U1.1108
N1109: J1204.1109, U1.1109
N1110: J921.1110, U1.1110
N1111: J900.1111, U1.1111
N1112: J83.1112, U1.1112
N1113: J957.1113, U1.1113
N1114: J1277.1114, U1.1114
N1115: J961.1115, U1.1115
N1116: J362.1116, U1.1116
N1117: J915.1117, U1.1117
N1118: J453.1118, U1.1118
N1119: J632.1119, U1.1119
N1120: J26.1120, U1.1120
N1121: J1104.1121, U1.1121
N1122: J378.1122, U1.1122
N1123: J849.1123, U1.1123
N1124: J512.1124, U1.1124
N1125: J911.1125, U1.1125
N1126: J1027.1126, U1.1126
N1127: J905.1127, U1.1127
N1128: J260.1128, U1.1128
N1129: J707.1129, U1.1129
N1130: J925.1130, U1.1130
N1131: J253.1131, U1.1131
N1132: J417.1132, U1.1132
N1133: J29.1133, U1.1133
N1134: J970.1134, U1.1134
N1135: J117.1135, U1.1135
N1136: J72.1136, U1.1136
N1137: J82.1137, U1.1137
N1138: J882.1138, U1.1138
N1139: J1156.1139, U1.1139
N1140: J212.1140, U1.1140
N1141: J39.1141, U1.1141
N1142: J590.1142, U1.1142
N1143: J199.1143, U1.1143
N1144: J697.1144, U1.1144
N1145: J887.1145, U1.1145
N1146: J1067.1146, U1.1146
N1147: J448.1147, U1.1147
N1148: J490.1148, U1.1148
N1149: J1119.1149, U1.1149
N1150: J184.1150, U1.1150
N1151: J1151.1151, U1.1151
N1152: J416.1152, U1.1152
N1153: J751.1153, U1.1153
N1154: J972.1154, U1.1154
N1155: J178.1155, U1.1155
N1156: J130.1156, U1.1156
N1157: J496.1157, U1.1157
N1158: J576.1158, U1.1158
N1159: J1011.1159, U1.1159
N1160: J621.1160, U1.1160
N1161: J754.1161, U1.1161
N1162: J1145.1162, U1.1162
N1163: J441.1163, U1.1163
N1164: J227.1164, U1.1164
N1165: J996.1165, U1.1165
N1166: J89.1166, U1.1166
N1167: J1057.1167, U1.1167
N1168: J58.1168, U1.1168
N1169: J391.1169, U1.1169
N1170: J1158.1170, U1.1170
N1171: J1262.1171, U1.1171
N1172: J788.1172, U1.1172
N1173: J1191.1173, U1.1173
N1174: J1018.1174, U1.1174
N1175: J1079.1175, U1.1175
N1176: J537.1176, U1.1176
N1177: J727.1177, U1.1177
N1178: J825.1178, U1.1178
N1179: J1192.1179, U1.1179
N1180: J243.1180, U1.1180
N1181: J1210.1181, U1.1181
N1182: J337.1182, U1.1182
N1183: J1031.1183, U1.1183
N1184: J171.1184, U1.1184
N1185: J1255.1185, U1.1185
N1186: J775.1186, U1.1186
N1187: J1293.1187, U1.1187
N1188: J86.1188, U1.1188
N1189: J954.1189, U1.1189
N1190: J1157.1190, U1.1190
N1191: J241.1191, U1.1191
N1192: J1248.1192, U1.1192
N1193: J1174.1193, U1.1193
N1194: J399.1194, U1.1194
N1195: J447.1195, U1.1195
N1196: J279.1196, U1.1196
N1197: J566.1197, U1.1197
N1198: J983.1198, U1.1198
N1199: J491.1199, U1.1199
N1200: J476.1200, U1.1200
N1201: J1122.1201, U1.1201
N1202: J1108.1202, U1.1202
N1203: J356.1203, U1.1203
N1204: J705.1204, U1.1204
N1205: J1215.1205, U1.1205
N1206: J1227.1206, U1.1206
N1207: J1142.1207, U1.1207
N1208: J1231.1208, U1.1208
N1209: J807.1209, U1.1209
N1210: J403.1210, U1.1210
N1211: J941.1211, U1.1211
N1212: J213.1212, U1.1212
N1213: J974.1213, U1.1213
N1214: J1264.1214, U1.1214
N1215: J12.1215, U1.1215
N1216: J596.1216, U1.1216
N1217: J654.1217, U1.1217
N1218: J196.1218, U1.1218
N1219: J348.1219, U1.1219
N1220: J1026.1220, U1.1220
N1221: J461.1221, U1.1221
N1222: J1237.1222, U1.1222
N1223: J252.1223, U1.1223
N1224: J234.1224, U1.1224
N1225: J1225.1225, U1.1225
N1226: J570.1226, U1.1226
N1227: J765.1227, U1.1227
N1228: J1014.1228, U1.1228
N1229: J1110.1229, U1.1229
N1230: J1017.1230, U1.1230
N1231: J1187.1231, U1.1231
N1232: J1160.1232, U1.1232
N1233: J622.1233, U1.1233
N1234: J164.1234, U1.1234
N1235: J309.1235, U1.1235
N1236: J153.1236, U1.1236
N1237: J686.1237, U1.1237
N1238: J736.1238, U1.1238
N1239: J822.1239, U1.1239
N1240: J1099.1240, U1.1240
N1241: J377.1241, U1.1241
N1242: J442.1242, U1.1242
N1243: J897.1243, U1.1243
N1244: J1244.1244, U1.1244
N1245: J747.1245, U1.1245
N1246: J244.1246, U1.1246
N1247: J165.1247, U1.1247
N1248: J1155.1248, U1.1248
N1249: J333.1249, U1.1249
N1250: J688.1250, U1.1250
N1251: J444.1251, U1.1251
N1252: J967.1252, U1.1252
N1253: J602.1253, U1.1253
N1254: J317.1254, U1.1254
N1255: J923.1255, U1.1255
N1256: J644.1256, U1.1256
N1257: J288.1257, U1.1257
N1258: J888.1258, U1.1258
N1259: J799.1259, U1.1259
N1260: J713.1260, U1.1260
N1261: J608.1261, U1.1261
N1262: J1125.1262, U1.1262
N1263: J1124.1263, U1.1263
N1264: J637.1264, U1.1264
N1265: J571.1265, U1.1265
N1266: J892.1266, U1.1266
N1267: J1216.1267, U1.1267
N1268: J664.1268, U1.1268
N1269: J1206.1269, U1.1269
N1270: J238.1270, U1.1270
N1271: J465.1271, U1.1271
N1272: J315.1272, U1.1272
N1273: J146.1273, U1.1273
N1274: J1046.1274, U1.1274
N1275: J744.1275, U1.1275
N1276: J502.1276, U1.1276
N1277: J1001.1277, U1.1277
N1278: J553.1278, U1.1278
N1279: J952.1279, U1.1279
N1280: J1291.1280, U1.1280
N1281: J251.1281, U1.1281
N1282: J206.1282, U1.1282
N1283: J387.1283, U1.1283
N1284: J783.1284, U1.1284
N1285: J45.1285, U1.1285
N1286: J938.1286, U1.1286
N1287: J77.1287, U1.1287
N1288: J679.1288, U1.1288
N1289: J308.1289, U1.1289
N1290: J293.1290, U1.1290
N1291: J172.1291, U1.1291
N1292: J773.1292, U1.1292
N1293: J535.1293, U1.1293
N1294: J190.1294, U1.1294
N1295: J1200.1295, U1.1295
N1296: J311.1296, U1.1296
